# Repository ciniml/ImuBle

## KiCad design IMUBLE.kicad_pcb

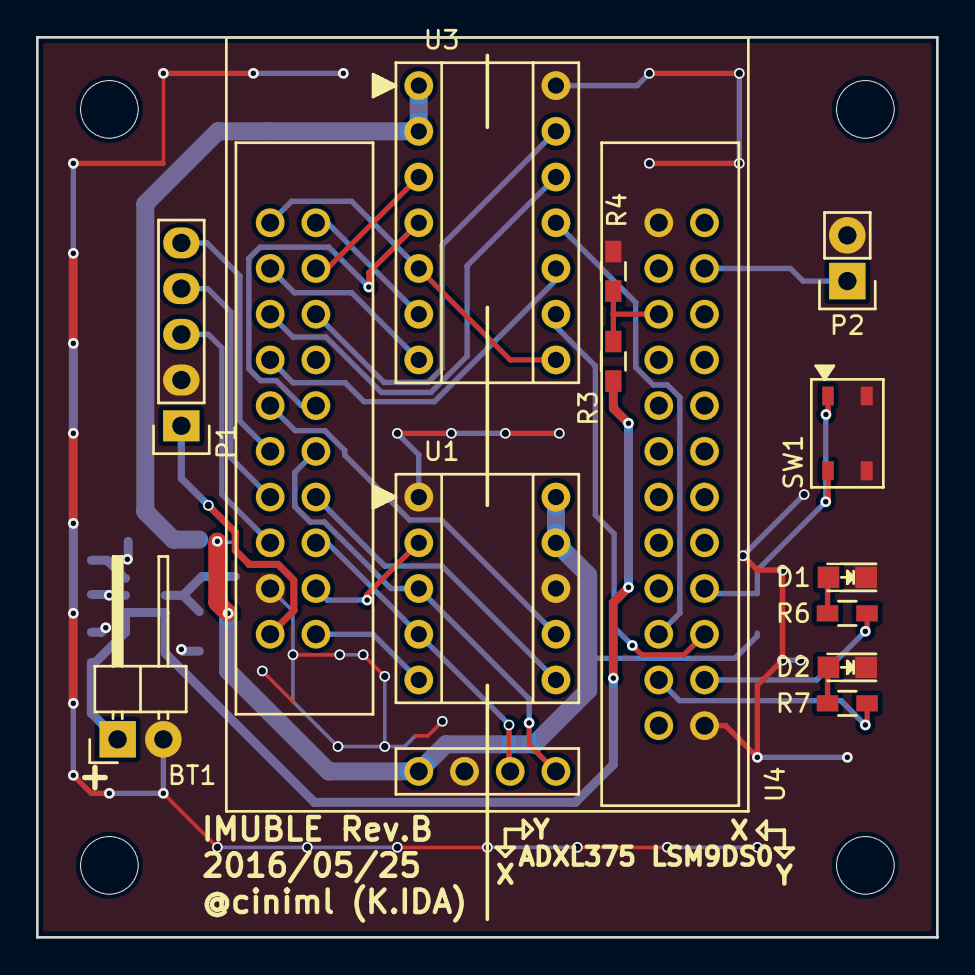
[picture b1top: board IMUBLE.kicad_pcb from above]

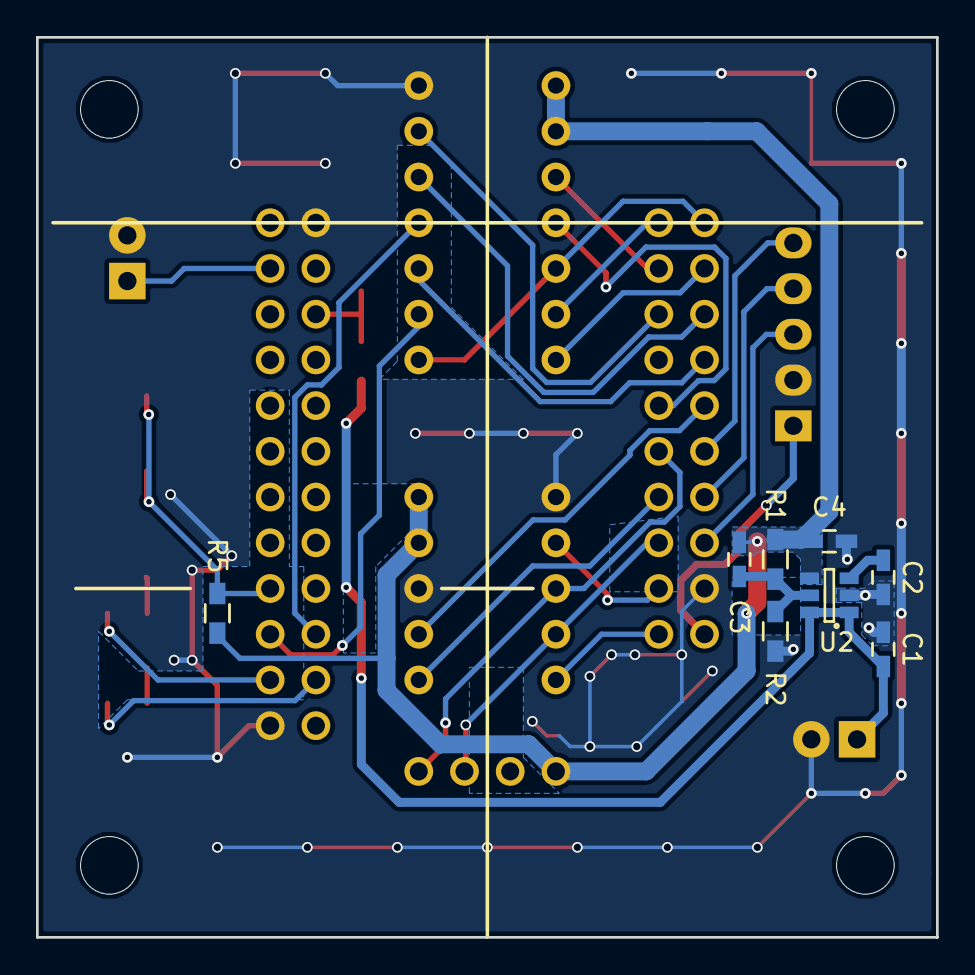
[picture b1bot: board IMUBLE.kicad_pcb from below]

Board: 2 copper layers, 50.0 x 50.0 mm, 25 parts (8 on the bottom side), 32 nets.

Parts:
BT1: CR2; Pin_Header_Angled_1x02
C1: 100n; C_0603_HandSoldering
C2: 10n; C_0603_HandSoldering
C3: 100p; C_0603_HandSoldering
C4: 1u; C_0603_HandSoldering
D1: RED; LED_0805
D2: GREEN; LED_0805
MH1, MH2, MH3, MH4: NPTH-M3
P1: CONN_01X05; Pin_Header_Straight_1x05
P2: DebugTX; Pin_Header_Straight_1x02
R1, R2, R5: 10k; R_0603_HandSoldering
R3: 2k; R_0603_HandSoldering
R4: 1k; R_0603_HandSoldering
R6, R7: 470; R_0603_HandSoldering
SW1: SKWPACE010; SKRPACE010
U1: SL_ADXL375; ST_ADXL375
U2: NJM11100; SOT-23-6
U3: SL_LSM9DS0; ST_LSM9DS0
U4: CY8CKIT-142

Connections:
+2.5V: C3.1, C4.1, R1.1, R5.1, U1.9, U1.10, U2.4, U3.1, U3.2, U4.VDD
+BATT: BT1.1, C1.1, R3.1, U2.1, U2.6
/ADX_CS: U1.5, U4.1.6
/ADX_INT1: U1.7, U4.1.2
/ADX_INT2: U1.6, U4.1.3
/ADX_MISO: U1.4, U4.1.5
/ADX_MOSI: U1.3, U4.1.4
/ADX_SCK: U1.2, U4.1.7
/LSM_CS_G: U3.3, U4.0.2
/LSM_CS_XM: U3.4, U4.1.1
/LSM_DEN: U3.9, U4.2.3
/LSM_DRDY: U3.11, U4.2.2
/LSM_INT1: U3.12, U4.0.5
/LSM_INT2: U3.13, U4.0.4
/LSM_INTG: U3.10, U4.1.0
/LSM_MISO: U3.5, U3.8, U4.0.1
/LSM_MOSI: U3.6, U4.0.0
/LSM_SCK: U3.7, U4.0.3
GND: BT1.2, C1.2, C2.2, C4.2, D1.1, D2.1, P1.2, P2.2, R2.2, R4.2, SW1.2, U1.1, U1.8, U2.2, U3.14, U4.GND
unnamed: C2.1, U2.3
unnamed: C3.2, R1.2, R2.1, U2.5
unnamed: D1.2, R6.2
unnamed: D2.2, R7.2
unnamed: P1.1, U4.VDDD
unnamed: P1.3, U4.XRES
unnamed: P1.4, U4.0.7
unnamed: P1.5, U4.0.6
unnamed: P2.1, U4.3.7
unnamed: R3.2, R4.1, U4.3.4
unnamed: R5.2, SW1.1, U4.2.5
unnamed: R6.1, U4.2.1
unnamed: R7.1, U4.2.0

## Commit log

2016-02-14 Add CY8CKIT-142 module and footprint
2016-04-26 Add Cypress_BLE.lib
2016-04-30 Fix programming pins of CY8CKIT-142
2016-04-30 Finished to design circuit.
2016-04-30 Add cache files and backup files to ignore list
2016-04-30 Add footprint for Strawbery Linux LSM9DS0 module.
2016-04-30 Add firmware source
2016-04-30 Add holder for CR2 type battery.
2016-05-02 Ignore .bak files
2016-05-02 Change character size of reference string
2016-05-02 Add ADXL375 and SMD push switch
2016-05-02 Annotate to schematic
2016-05-02 Ignore pcb-bak files
2016-05-02 Finished initial component layout
2016-05-02 Change pin assignment of CY8CKIT-142 and update some pin attribute to pass the ERC
2016-05-02 Add mechanical hole for M3 bolt
2016-05-02 Finished to layout
2016-05-02 Update pin assignment
2016-05-02 Shrink pad size of IMU modules
2016-05-03 Remove some floating/parasistic-antenna GND patterns
2016-05-03 Release gerber data to Elecrow (Rev.A)
2016-05-19 Implement reading LSM9DS0 sensor
2016-05-19 Implement reading sensor data from ADXL375.
2016-05-19 Add Update Interval characteristic
2016-05-24 Fix that register index is wrong when reading from the OUT_X_M and OUT_X_A registers
2016-05-24 Fix that ADOR bit definition is wrong
2016-05-24 Fix that sensor data is not updated periodically.
2016-05-24 Update VS projects
2016-05-24 Add host software
2016-05-27 Add UART module for debugging
2016-06-06 Fix that gyro HPF cutoff is too high (50HZ). Fix that magnetometer register index is wrong
2016-06-12 Add programming signals to CY8CKIT-142
2016-06-12 Change MTU to 23
2016-06-12 Ignore packages
2016-06-12 Add recorder GUI project
2016-07-24 Add support for STEVAL-WeSU1
2016-07-24 Add LICENSE
